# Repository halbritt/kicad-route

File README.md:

# kicad-route

Agent-driven PCB trace routing for KiCad projects, graded by KiCad itself.

`kicad-route` runs a routing backend — its built-in router (`builtin`), or
[Freerouting](https://github.com/freerouting/freerouting) — on an isolated copy of a
KiCad project and hands back a native KiCad candidate board. The candidate is then graded
with `kicad-cli` DRC (zones refilled, schematic parity) against the input's own,
unchanged rules, plus checks that the backend preserved what it must not touch: outline,
layers, stackup, net classes, footprints, zones, keepouts, existing copper, net-class
widths and pour integrity. Backend relaxations are switched off, and anything they still
slip through is caught by the grading rather than trusted.

The result is structured for an agent to read and act on: process, routing and
validation are reported separately, with exit codes 0 (complete and valid), 1 (process
failure, no candidate), 2 (valid but incomplete), 3 (fails validation) and 4 (refused
before routing: a usage or input error, the ledger, the `--canary` pre-flight, a board
without a `.kicad_pro` of its own name, or a writable state directory under
`--require-readonly-state`, with a refusal record). Programs calling it use the versioned
machine interface: `--json` prints one schema-carrying record on stdout ([`docs/interface.md`](docs/interface.md),
[`schemas/`](schemas/)).

## Install

Requirements: Linux, KiCad 10 with its Python bindings for `/usr/bin/python3`
(`kicad-cli`, `pcbnew`), `git`, [`uv`](https://docs.astral.sh/uv/), a Rust toolchain
with Cargo and C build tools (`build-essential` on Debian/Ubuntu) to build the
owned engine, and a Java runtime new
enough for the current Freerouting jar (Java 25 for 2.5.x:
`sudo apt install openjdk-25-jre-headless`). `pytest` and `jsonschema` for `smoke` (test-only).
The `planes` command also requires Bubblewrap (`bwrap`) on PATH.

```sh
git clone https://github.com/halbritt/kicad-route ~/git/kicad-route
~/git/kicad-route/scripts/install.sh      # CLI + skill links, then `kicad-route update`
kicad-route doctor
```

`install.sh` links `~/.local/bin/kicad-route` and the `kicad-route` agent skill into
`~/.agents/skills`, `~/.codex/skills` and `~/.claude/skills`. `kicad-route update`
builds the built-in router from this repository and installs Freerouting's current
release. The versions and source hashes used are recorded in every result.
It generates the `krt-*` diagnostic skills (names retained for compatibility)
from the included source, and runs the integration tests. Re-run it to update.

## Use

`builtin` is the default backend. Its Python and Rust source is part of kicad-route:
upstream [KRT (KiCadRoutingTools)](https://github.com/drandyhaas/KiCadRoutingTools) at a
recorded commit plus a small set of local changes ([`docs/upstream-engine.md`](docs/upstream-engine.md));
it does not require a separate KRT checkout or download. `--backend krt` remains a
deprecated alias and warns on stderr; new results identify the backend as `builtin`.
Existing receipts remain readable. State-manifest and determinism `krt` keys,
identity fingerprints, `work/krt.log`, and generated `krt-*` skill names retain
their compatibility spelling.

From a KiCad project directory:

```sh
kicad-route run --backend builtin                          # all nets, 300 s budget
kicad-route run --backend builtin --diff-pairs auto        # native-class pairs first, then other nets
kicad-route run --backend builtin --diff-pairs auto --grid-step 0.025  # finer search for narrow pad escapes
kicad-route run --backend builtin --length-match-group DQ0 DQ1 DQ2 DQ3 --group-match-tolerance 0.1
kicad-route run --backend builtin --length-match-group DQ0 DQ1 --group-delay-tolerance 1  # authored native timing profiles
kicad-route run --backend builtin --diff-pairs auto --pair-layers F.Cu In1.Cu In2.Cu B.Cu  # enabled pair track layers
kicad-route run --backend freerouting --nets "/CAN*" --clearance-margin 0.01
kicad-route run --backend builtin --rev HEAD --budget 1500 # route the committed state
kicad-route validate build/kicad-route/runs/<project>/<label>/latest
kicad-route compare <run_dir> <run_dir>
kicad-route run --backend builtin --reserve-spokes         # keep new copper off thermal-spoke corridors
kicad-route run --backend builtin --dir <run>/candidate/<project> --protect human
                                                       # continue a chain; earlier agent copper may be rerouted
kicad-route campaign --backend builtin --rounds 2          # hard nets first, best chain graded vs the input
kicad-route blocked <run_dir>                          # what lies across each open connection
kicad-route blocked --board <B>.kicad_pcb --json      # the same for a placed board, before routing
kicad-route spokes <run_dir>                           # which new copper starved which thermal pad
kicad-route audit --old HEAD~1                         # grade the last commit's board change
kicad-route floor                                      # rules looser than their high-water mark / declared floor
kicad-route run --backend builtin --json --run-dir /tmp/r1 # machine mode: one JSON record on stdout, logs on stderr
kicad-route run --backend builtin --barrier-from <run>      # retry with a keepout where that run's new copper collided
kicad-route decoupling --board <B>.kicad_pcb          # read-only: bypass capacitors between IC pins and the plane?
kicad-route planes --board B.kicad_pcb --plan plane-plan.json --run-dir build/planes-1 --json
                                                       # explicit native planes with refill evidence
kicad-route doctor --json --offline                    # readiness, and what a sandbox must provide
```

Runs go under `./build/kicad-route/runs/<project>/<label>/<stamp>/` (`--out`, before or
after the subcommand, or `$KICAD_ROUTE_OUT` to change; `run --run-dir PATH` to choose
the directory); the candidate is `candidate/<project>/<board>.kicad_pcb`,
the verdict `result.json` (and `RESULT.md`). The project itself is never modified.

A project can wrap the commands in its own targets, for example:

```make
ROUTE := kicad-route --out build/route
route:
	$(ROUTE) run --backend $(BACKEND) --rev $(REV) --budget $(BUDGET) $(ARGS)
```

## Documentation

New here? Start with the **[guide](docs/guide/README.md)**: an overview with
diagrams, a walk-through on the bundled demo board (with before/after figures), how a
run works stage by stage, how to read results, real-board workflows, automation and
sandboxes, and a glossary. The pages below are the reference.

- [`docs/interface.md`](docs/interface.md) — the machine contract: record kinds and
  schema ids (`schemas/result-1.json`, `schemas/result-2.json`, `schemas/refusal-1.json`), what each exit code
  promises, refusal records, `--json`, `--run-dir`, stable fields and versioning.
- [`docs/routing.md`](docs/routing.md) — backends and what the adapters switch off,
  run layout and result semantics, native grading, preservation checks, `audit`,
  installation and updates, decisions, known limitations, fixture evidence.
- [`docs/upstream-engine.md`](docs/upstream-engine.md) — the builtin router is upstream
  KRT at a recorded commit plus a small listed set of local changes; the one command
  that moves it to a newer upstream commit.
- [`docs/routing-engine-migration.md`](docs/routing-engine-migration.md) — how the
  router came into this repository (2026-10-20), its build and that migration's
  acceptance requirements.
- [`docs/campaign.md`](docs/campaign.md) — `campaign`: automated hard-nets-first chains,
  backlog rounds, ranking, race orderings.
- [`docs/floor.md`](docs/floor.md) — rule high-water mark and the declared rule floor
  (`<board>.rules-floor.json`) used by `floor`, `audit` and the `run` pre-flight.
- [`docs/blocked.md`](docs/blocked.md) — blocked-by receipts for incomplete runs: what
  lies across each open connection, and a rip-up ranking (`kicad-route blocked`).
- [`docs/hygiene.md`](docs/hygiene.md) — run hygiene: `--stall` progress watchdog,
  the run ledger (exit 4 on an exact repeat of a failed attempt), the awkward-net-name
  canary, and the real-board `corpus` gate that `update` runs.
- [`docs/spokes.md`](docs/spokes.md) — `--reserve-spokes`: temporary keepouts on thermal-spoke
  corridors while routing (removed before grading), and `kicad-route spokes` attribution.
- [`docs/decoupling.md`](docs/decoupling.md) — `kicad-route decoupling`: read-only audit of bypass
  capacitor cells (pin → capacitor → plane, or a direct pin via that bypasses the capacitor).
- [`docs/barrier.md`](docs/barrier.md) — `--barrier-from RUN_DIR`: reroute with a small temporary keepout where a run's new copper collided (removed before grading).
- [`docs/closed.md`](docs/closed.md) — what a board closes to new copper without a rule area (solder-mask
  apertures that are not pad openings, copper without a net): closed with temporary keepouts on every run,
  removed before grading.
- [`docs/provenance.md`](docs/provenance.md) — `--protect human`: in a `--dir` chain only the
  designer's copper is protected, and the `net_completion` ratchet.
- [`docs/planes.md`](docs/planes.md) — exact `agent-ee.plane-plan/1` zone production,
  native refill evidence and before/after pour integrity (`kicad-route planes`).
- [`docs/pour.md`](docs/pour.md) — the `pour_integrity` check: pad fill contact, thermal
  spokes and pour islands compared between the refilled input and candidate.
- [`docs/sandbox.md`](docs/sandbox.md) — running in a sandbox: what `doctor --json --offline`
  says a sandbox must provide, `--require-readonly-state`, `--ledger`, nothing under HOME.
- [`skills/kicad-route/SKILL.md`](skills/kicad-route/SKILL.md) — the agent-facing guide,
  including the retry playbook.
- `reports/fixture/` — the latest committed smoke evidence (`make evidence`);
  `reports/state/manifest.json` — the state manifest of the install that produced it;
  `reports/determinism/` — the historical KRT repeat check for that build (`make determinism`).

## Development

```sh
make install          # scripts/install.sh: CLI and skill links, then update
make doctor | update | smoke
make state-manifest   # record the installed backends in STATE/manifest.json (no downloads)
make determinism      # route the fixture twice with builtin, compare, record the verdict
make evidence     # smoke, then publish its structured evidence to reports/fixture/
make fixture      # regenerate fixtures/route_demo
```

Tests and lab rounds run through [mise](https://mise.jdx.dev) tasks (`mise.toml`). Each
wraps the command above or a pytest call, and the ones that start engines or KiCad go
through the host's shared `host:exec` task, which waits for host capacity, enforces a
deadline and stops everything the run started:

```sh
mise tasks ls                                  # what there is
mise run test -- tests/test_stitch.py          # focused pytest files or test IDs
mise run test:engine                           # the owned engine's regression scripts
mise run test:kernel                           # make kernel
mise run test:smoke                            # make smoke
mise run test:suite                            # every file under tests/, about an hour
mise run lab:run -- r16 --budget 300 --jobs 3 -- --recipe auto    # a router lab round (lab/README.md)
```

`HOST_TEST_TIMEOUT=2h` (or `LAB_TIMEOUT` for a lab round) overrides a deadline. A lab
round asks for one unit of host capacity per job; a host that is busy refuses it
(exit 75) and the round is started again later. A worktree needs the built routing
environment (`.venv-krt`) for the tests that route.

## License

kicad-route itself is MIT-licensed ([`LICENSE`](LICENSE)).

The owned routing engine derives from MIT-licensed
[KRT](https://github.com/drandyhaas/KiCadRoutingTools), copyright drandyhaas.
Its license and source provenance are retained in
[`src/kicad_route/router/`](src/kicad_route/router/). It runs in a separate worker
process, using a Rust extension built from the included source.

[Freerouting](https://github.com/freerouting/freerouting) is GPL-3.0 and remains a
separate program, acquired into the git-ignored `STATE/vendor/freerouting` directory.
It is not redistributed, imported or linked by kicad-route.

The owned routing kernels have a separate fast gate: `make kernel`. See
[`docs/kernel-testing.md`](docs/kernel-testing.md) for its dependencies, mutation
proof, upstream test inventory and boundaries; native `make smoke` remains required.

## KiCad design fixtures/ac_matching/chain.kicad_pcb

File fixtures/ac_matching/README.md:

Software qualification article: four layers, two fixed 2.54mm terminal pairs and two populated 0402 100nF series capacitors. C1 bridges P and C2 bridges N between DPA and DPB. Each segment spans approximately30mm; capacitor pad separation is0.96mm and the P/N capacitor pitch is4mm. The native width/gap are0.15/0.25mm, local skew budget0.2mm, and terminal escape budget4mm persegment. The composed terminal-to-terminal copper P/N skew requirement is0.1mm. All are explicit agent-selected software qualification assumptions; no physical protocol, capacitor internal delay, impedance or manufacturing acceptance is asserted. Actual native useful-path contributions across both named segments must be measured after routing; backend success/skew flags cannot establish acceptance. Initial generation derives footprint geometry from installed KiCad libraries and retains the exact local dependencies.

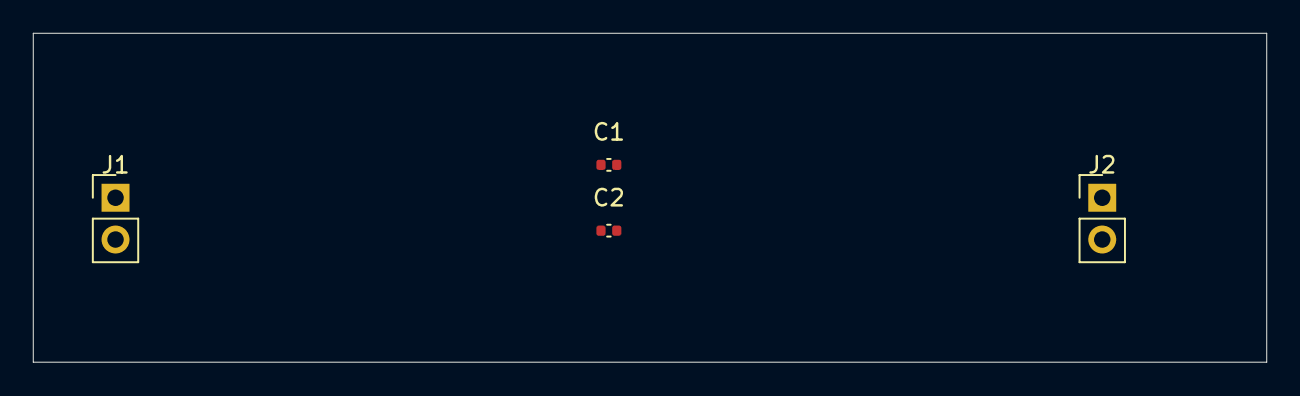
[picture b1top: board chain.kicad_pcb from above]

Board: 4 copper layers, 75.0 x 20.0 mm, 4 parts (0 on the bottom side), 4 nets, no tracks yet.

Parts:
C1, C2: 100nF; C0402
J1, J2: Qualification terminal; Terminal2

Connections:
DPA_N: C2.1, J1.2
DPA_P: C1.1, J1.1
DPB_N: C2.2, J2.2
DPB_P: C1.2, J2.1

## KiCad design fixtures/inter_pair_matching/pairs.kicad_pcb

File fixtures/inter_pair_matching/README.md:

Agent-selected software qualification assumptions: four layers; fixed SMD terminal pairs with 50 and 60 mm direct paths, 0.25 mm width/0.35 mm gap, 0.15 mm group skew, 0.1 mm intra-pair skew, 3 mm maximum uncoupled extent (5 percent of the approximately 60 mm useful path). No impedance, circuit, assembly or manufacturing acceptance is claimed. Native group skew checks all four useful paths, a stated requirement, not an average of paired legs.

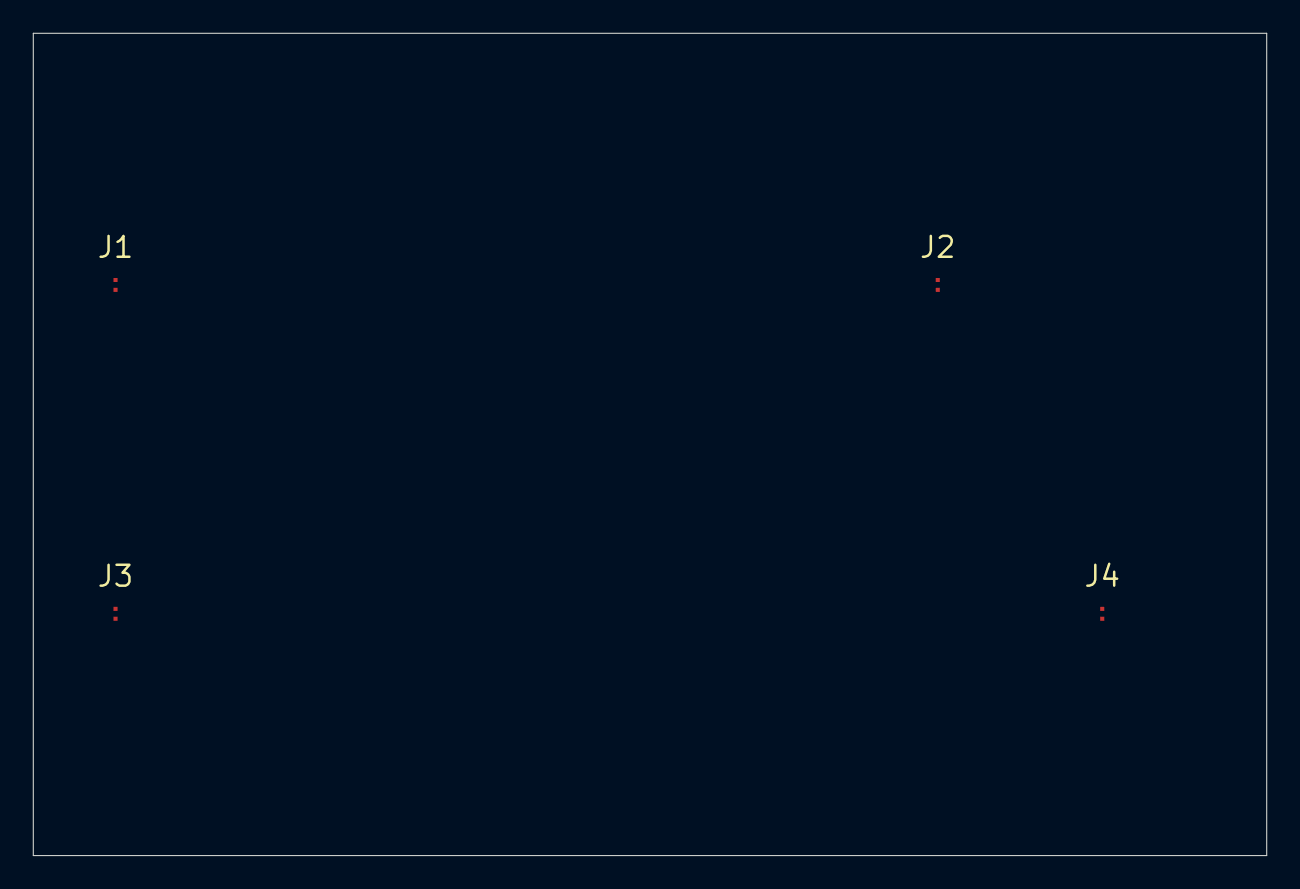
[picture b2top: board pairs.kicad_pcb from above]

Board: 4 copper layers, 75.0 x 50.0 mm, 4 parts (0 on the bottom side), 4 nets, no tracks yet.

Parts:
J1, J2, J3, J4: Qualification terminal pair; Terminal2

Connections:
A_N: J1.2, J2.2
A_P: J1.1, J2.1
B_N: J3.2, J4.2
B_P: J3.1, J4.1

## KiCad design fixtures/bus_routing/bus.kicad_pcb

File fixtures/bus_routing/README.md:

# Native bus-routing article

This generated software qualification board has eight parallel nets D0–D7
between fixed native 2.54 mm headers, a third terminal on D3, and a separate
parallel AUX connection. A routing-only rule area on F.Cu obstructs the upper
lanes. The stock header modules and their library license are captured locally.

The native project requires 0.25 mm track width and 0.2 mm class clearance;
its board floors and rule severities remain authoritative. The 70 by 65 mm
outline and fixed footprint coordinates are part of the input. A 20 mm bus
endpoint-clustering radius and minimum three members are agent-selected search
preferences, not electrical acceptance criteria.

Exercise with `kicad-route run --dir fixtures/bus_routing --bus
--bus-detection-radius 20 --bus-min-nets 3 --diff-pairs auto --grid-step .1`.
The final saved board must have no opens or native findings and preserve input
constraints. Actual backend diagnostics should identify D0–D7 as a geometric
bus, exclude AUX and connect all three D3 terminals. Geometric grouping does
not establish electrical bus identity, timing, impedance or manufacturability.

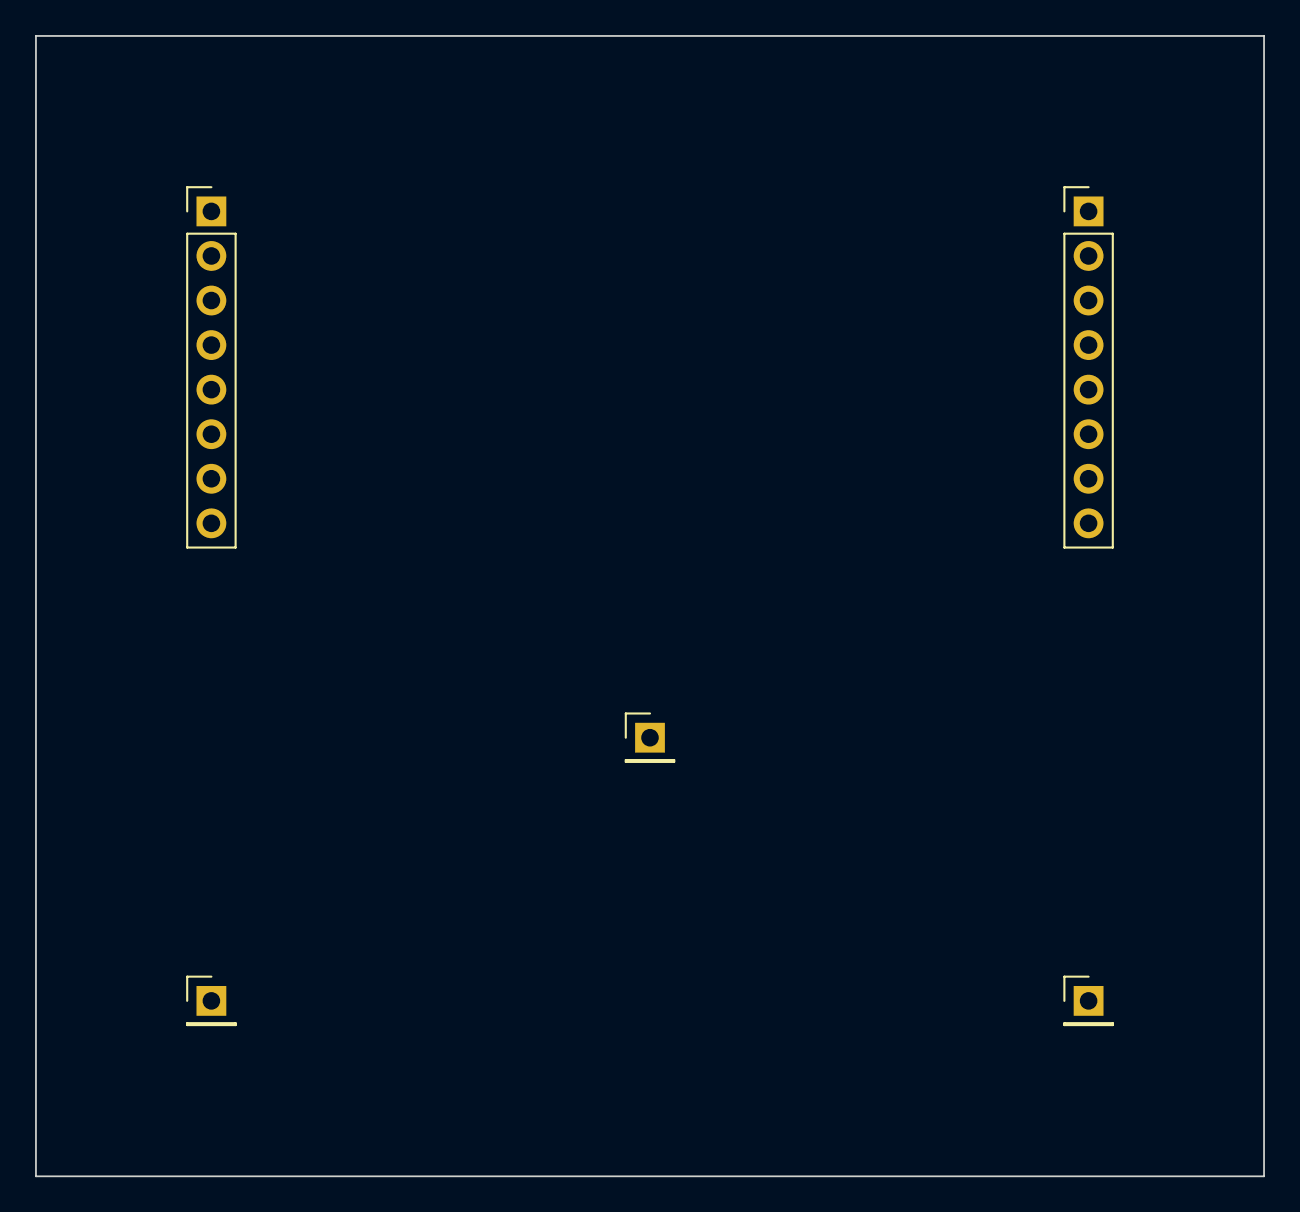
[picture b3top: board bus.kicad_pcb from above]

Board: 2 copper layers, 70.0 x 65.0 mm, 5 parts (0 on the bottom side), 9 nets, no tracks yet.

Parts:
J1, J2: PinHeader_1x08_P2.54mm_Vertical
J3, J4: PinHeader_1x01_P2.54mm_Vertical
TP1: PinHeader_1x01_P2.54mm_Vertical

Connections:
AUX: J3.1, J4.1
D0: J1.1, J2.1
D1: J1.2, J2.2
D2: J1.3, J2.3
D3: J1.4, J2.4, TP1.1
D4: J1.5, J2.5
D5: J1.6, J2.6
D6: J1.7, J2.7
D7: J1.8, J2.8

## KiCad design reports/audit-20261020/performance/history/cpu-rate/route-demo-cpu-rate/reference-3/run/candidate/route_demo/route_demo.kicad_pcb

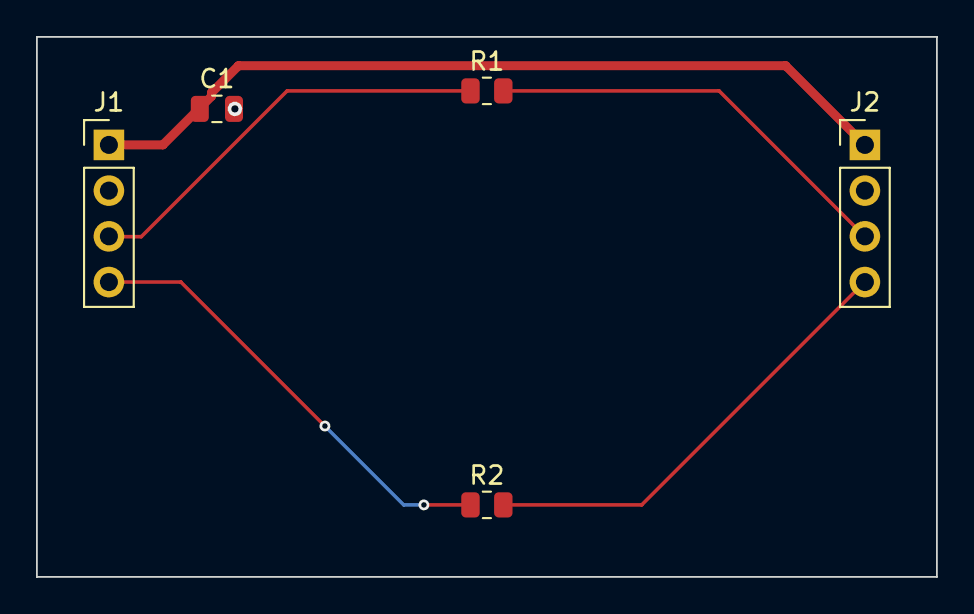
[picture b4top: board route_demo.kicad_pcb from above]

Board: 2 copper layers, 50.0 x 30.0 mm, 5 parts (0 on the bottom side), 6 nets.

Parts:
C1: 1u; C_0805_2012Metric
J1, J2: Conn_01x04; PinHeader_1x04_P2.54mm_Vertical
R1, R2: 33; R_0805_2012Metric

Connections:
/SIG_A: J1.3, R1.1
/SIG_A_OUT: J2.3, R1.2
/SIG_B: J1.4, R2.1
/SIG_B_OUT: J2.4, R2.2
/VIN: C1.1, J1.1, J2.1
GND: C1.2, J1.2, J2.2
